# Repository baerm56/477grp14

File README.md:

# 477grp14
This is our senior design project

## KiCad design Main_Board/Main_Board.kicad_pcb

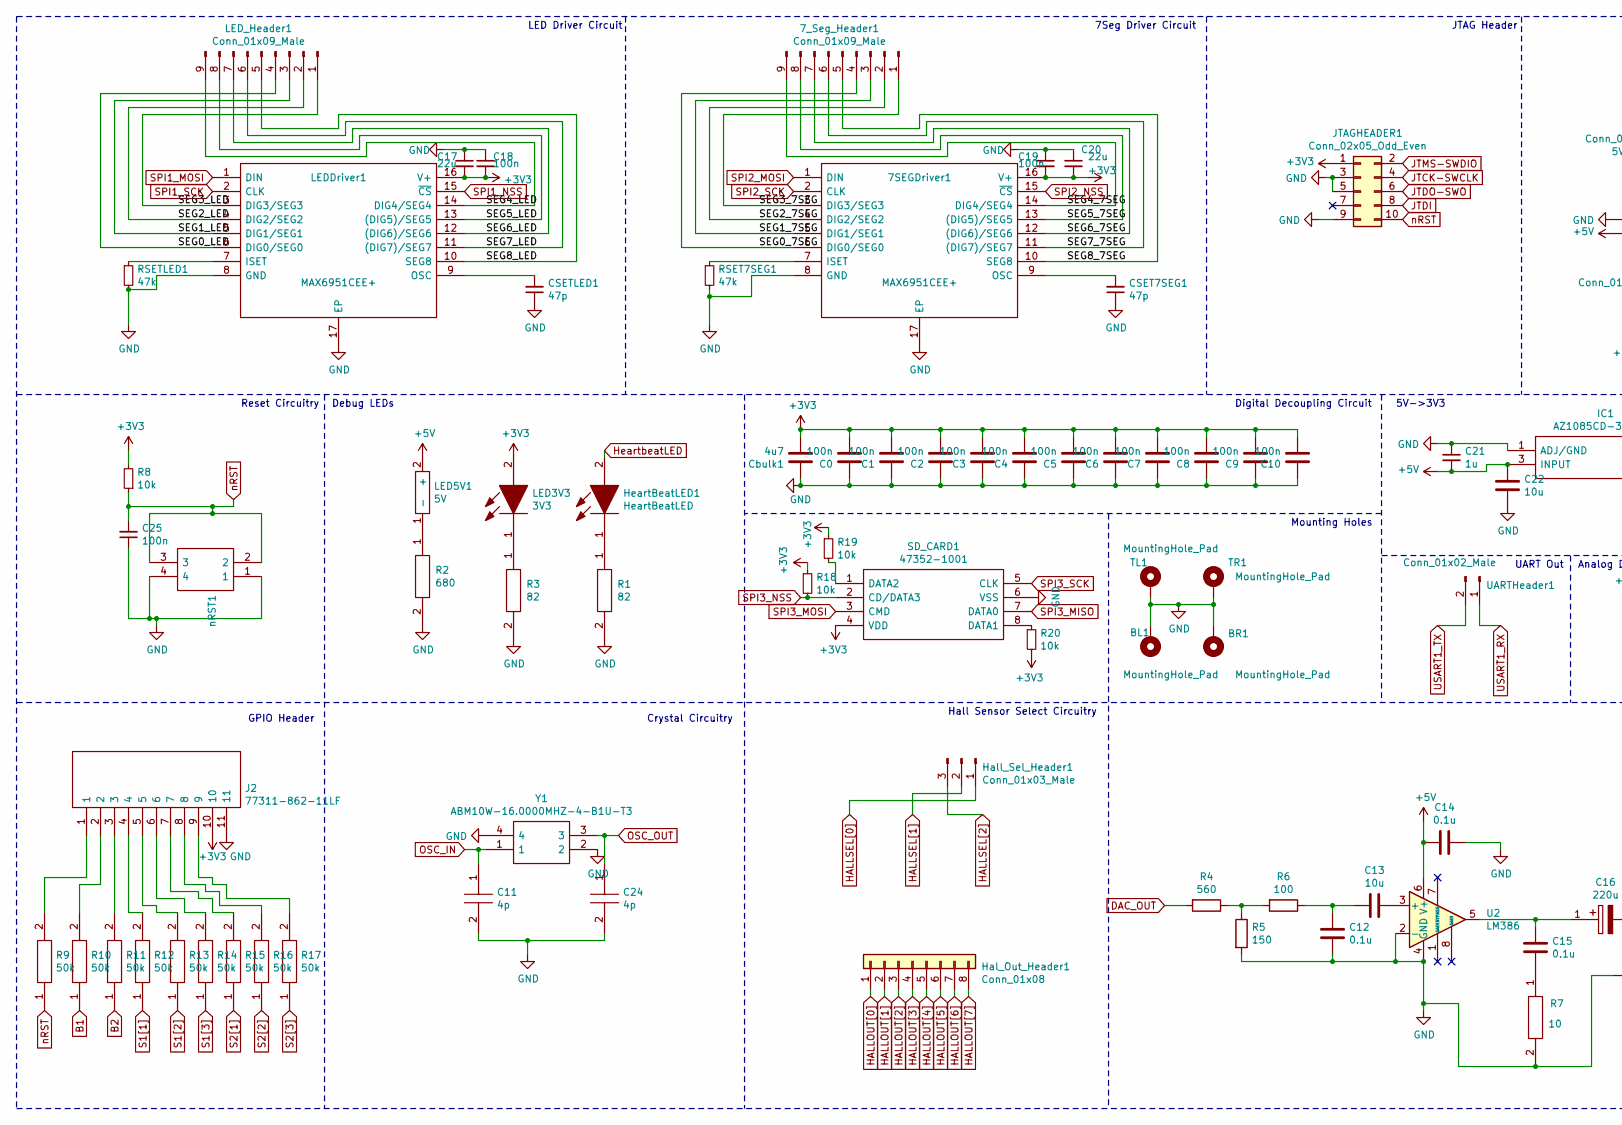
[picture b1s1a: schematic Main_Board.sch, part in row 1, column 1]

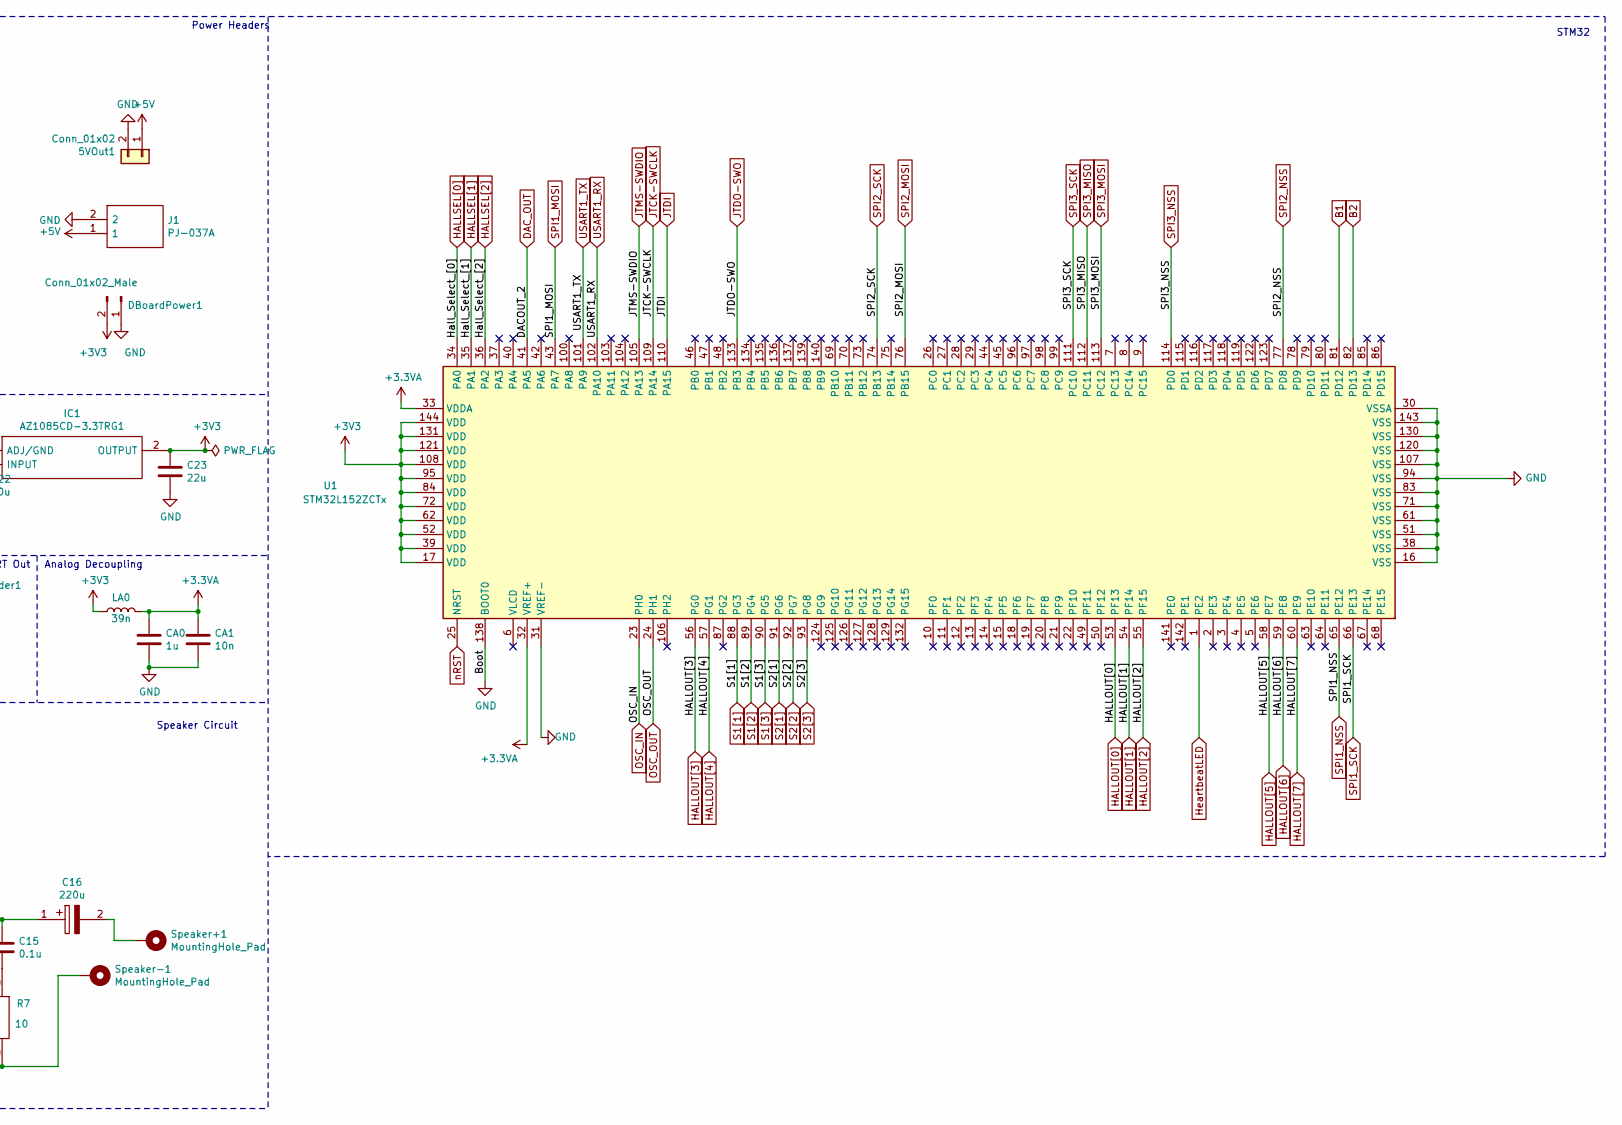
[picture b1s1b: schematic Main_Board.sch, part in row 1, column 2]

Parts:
5VOut1: Conn_01x02; PinHeader_1x02_P2.54mm_Vertical
7SEGDriver1: MAX6951CEE+; SOP64P602X173-17N; Mouser Part Number 700-MAX6951CEE
7_Seg_Header1: Conn_01x09_Male; PinHeader_1x09_P2.54mm_Vertical
BL1: MountingHole_Pad; MountingHole_4.3mm_M4_Pad_Via
BR1: MountingHole_Pad; MountingHole_4.3mm_M4_Pad_Via
C0, C1, C2, C3, C4, C5, C6, C7, C8, C9, C10, C18, C19, C25: 100n; CAPC2012X95N
C11, C24: 4p; CAPC1005X55N; Manufacturer_Part_Number GCQ1555C1H4R0CB01D
C12, C14, C15: 0.1u; CAPC2012X95N
C13, C22: 10u; CAPC2012X140N
C16: 220u; CAPPRD200W55D500H1200; Mouser Part Number 667-ECA-0JHG221B
C17, C20, C23: 22u; C1608_Commercial
C21: 1u; CAPC1005X55N
CA0: 1u; CAPC1005X55N
CA1: 10n; CAPC0402X22N
CSET7SEG1: 47p; CAPC2012X75N
CSETLED1: 47p; CAPC2012X75N
Cbulk1: 4u7; CAPPRD200W52D500H1250
DBoardPower1: Conn_01x02_Male; PinHeader_1x02_P2.54mm_Vertical
Hal_Out_Header1: Conn_01x08; PinHeader_1x08_P2.54mm_Vertical
Hall_Sel_Header1: Conn_01x03_Male; PinHeader_1x03_P2.54mm_Vertical
HeartBeatLED1: HeartBeatLED; LEDM168X65N; Mouser Part Number 755-SMLD12BN1WT86
IC1: AZ1085CD-3.3TRG1; AZ1085CD33TRG1; Mouser Part Number 621-AZ1085CD-3.3TRG1
J1: PJ-037A; PJ037A; Mouser Part Number 490-PJ-037A
J2: 77311-862-11LF; HDRV11W62P0X254_1X11_2794X240X853P; Manufacturer_Part_Number 77311-862-11LF
JTAGHEADER1: Conn_02x05_Odd_Even; PinHeader_2x05_P2.54mm_Vertical
LA0: 39n; LQW2UAS12NG00L
LED3V3: 3V3; LEDM168X65N; Mouser Part Number 755-SMLD12BN1WT86
LED5V1: 5V; HSMA-C380
LEDDriver1: MAX6951CEE+; SOP64P602X173-17N; Mouser Part Number 700-MAX6951CEE
LED_Header1: Conn_01x09_Male; PinHeader_1x09_P2.54mm_Vertical
R1, R3: 82; RESC6432X65N; Mouser Part Number 279-CRGP2512F82R
R2: 680; RESC3116X70N; Mouser Part Number 667-ERJ-UP8F6800V
R4: 560; CRGCQ2512F3K3
R5: 150; ERJ1TRQF1R0U
R6: 100; RESC5025X70N
R7: 10; RESC5025X120N; Mouser Part Number 279-350210RFT
R8, R18, R19, R20: 10k; RESC3116X70N
R9, R10, R11, R12, R13, R14, R15, R16, R17: 50k; RESC1005X40N; Mouser Part Number 71-CRCW0402-50K-E3
RSET7SEG1: 47k; RESC2012X60N
RSETLED1: 47k; RESC2012X60N
SD_CARD1: 47352-1001; Mouser Part Number 538-47352-1001
Speaker+1: MountingHole_Pad; MountingHole_2.5mm_Pad
Speaker-1: MountingHole_Pad; MountingHole_2.5mm_Pad
TL1: MountingHole_Pad; MountingHole_4.3mm_M4_Pad_Via
TR1: MountingHole_Pad; MountingHole_4.3mm_M4_Pad_Via
U1: STM32L152ZCTx; LQFP-144_20x20mm_P0.5mm
U2: LM386; SOIC127P600X175-8N
UARTHeader1: Conn_01x02_Male; PinHeader_1x02_P2.54mm_Vertical
Y1: ABM10W-16.0000MHZ-4-B1U-T3; ABM10W400000MHZ4K1ZT3; Mouser Part Number 815-10W16-4B1UT
nRST1: A; PTS647SM50SMTR2LFS; Mouser Part Number 611-PTS647SM50SMTR2L

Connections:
+3.3VA: CA0.1, CA1.1, LA0.2, U1.32 (VREF+), U1.33 (VDDA)
+3V3: 7SEGDriver1.16 (V+), C0.2, C1.2, C2.2, C3.2, C4.2, C5.2, C6.2, C7.2, C8.2, C9.2, C10.2, C17.2, C18.2, C19.2, C20.2, C23.1, Cbulk1.2, DBoardPower1.2, IC1.2 (OUTPUT), J2.10, JTAGHEADER1.1, LA0.1, LED3V3.2, LEDDriver1.16 (V+), R8.2, R18.1, R19.1, R20.2, SD_CARD1.4 (VDD), U1.17 (VDD), U1.39 (VDD), U1.52 (VDD), U1.62 (VDD), U1.72 (VDD), U1.84 (VDD), U1.95 (VDD), U1.108 (VDD), U1.121 (VDD), U1.131 (VDD), U1.144 (VDD)
+5V: 5VOut1.1, C14.2, C21.2, C22.1, IC1.3 (INPUT), J1.1, LED5V1.2 (+), U2.6 (V+)
/SEG0_7SEG: 7SEGDriver1.6 (DIG0/SEG0), 7_Seg_Header1.4
/SEG0_LED: LEDDriver1.6 (DIG0/SEG0), LED_Header1.4
/SEG1_7SEG: 7SEGDriver1.5 (DIG1/SEG1), 7_Seg_Header1.3
/SEG1_LED: LEDDriver1.5 (DIG1/SEG1), LED_Header1.3
/SEG2_7SEG: 7SEGDriver1.4 (DIG2/SEG2), 7_Seg_Header1.2
/SEG2_LED: LEDDriver1.4 (DIG2/SEG2), LED_Header1.2
/SEG3_7SEG: 7SEGDriver1.3 (DIG3/SEG3), 7_Seg_Header1.1
/SEG3_LED: LEDDriver1.3 (DIG3/SEG3), LED_Header1.1
/SEG4_7SEG: 7SEGDriver1.14 (DIG4/SEG4), 7_Seg_Header1.9
/SEG4_LED: LEDDriver1.14 (DIG4/SEG4), LED_Header1.9
/SEG5_7SEG: 7SEGDriver1.13 ((DIG5)/SEG5), 7_Seg_Header1.8
/SEG5_LED: LEDDriver1.13 ((DIG5)/SEG5), LED_Header1.8
/SEG6_7SEG: 7SEGDriver1.12 ((DIG6)/SEG6), 7_Seg_Header1.7
/SEG6_LED: LEDDriver1.12 ((DIG6)/SEG6), LED_Header1.7
/SEG7_7SEG: 7SEGDriver1.11 ((DIG7)/SEG7), 7_Seg_Header1.6
/SEG7_LED: LEDDriver1.11 ((DIG7)/SEG7), LED_Header1.6
/SEG8_7SEG: 7SEGDriver1.10 (SEG8), 7_Seg_Header1.5
/SEG8_LED: LEDDriver1.10 (SEG8), LED_Header1.5
B1: R10.1, U1.81 (PD12)
B2: R11.1, U1.82 (PD13)
DAC_OUT: R4.2, U1.41 (PA5)
GND: 5VOut1.2, 7SEGDriver1.8 (GND), 7SEGDriver1.17 (EP), BL1.1, BR1.1, C0.1, C1.1, C2.1, C3.1, C4.1, C5.1, C6.1, C7.1, C8.1, C9.1, C10.1, C11.2, C12.2, C14.1, C17.1, C18.1, C19.1, C20.1, C21.1, C22.2, C23.2, C24.2, C25.1, CA0.2, CA1.2, CSET7SEG1.1, CSETLED1.1, Cbulk1.1, DBoardPower1.1, IC1.1 (ADJ/GND), J1.2, J2.11, JTAGHEADER1.3, JTAGHEADER1.5, JTAGHEADER1.9, LEDDriver1.8 (GND), LEDDriver1.17 (EP), R1.2, R2.2, R3.2, R5.2, R7.2, RSET7SEG1.2, RSETLED1.2, SD_CARD1.6 (VSS), Speaker-1.1, TL1.1, TR1.1, U1.16 (VSS), U1.30 (VSSA), U1.31 (VREF-), U1.38 (VSS), U1.51 (VSS), U1.61 (VSS), U1.71 (VSS), U1.83 (VSS), U1.94 (VSS), U1.107 (VSS), U1.120 (VSS), U1.130 (VSS), U1.138 (BOOT0), U1.143 (VSS), U2.2 (-), U2.4 (GND), Y1.2, Y1.4, nRST1.1, nRST1.4
HALLOUT[0]: Hal_Out_Header1.1, U1.53 (PF13)
HALLOUT[1]: Hal_Out_Header1.2, U1.54 (PF14)
HALLOUT[2]: Hal_Out_Header1.3, U1.55 (PF15)
HALLOUT[3]: Hal_Out_Header1.4, U1.56 (PG0)
HALLOUT[4]: Hal_Out_Header1.5, U1.57 (PG1)
HALLOUT[5]: Hal_Out_Header1.6, U1.58 (PE7)
HALLOUT[6]: Hal_Out_Header1.7, U1.59 (PE8)
HALLOUT[7]: Hal_Out_Header1.8, U1.60 (PE9)
HALLSEL[0]: Hall_Sel_Header1.1, U1.34 (PA0)
HALLSEL[1]: Hall_Sel_Header1.2, U1.35 (PA1)
HALLSEL[2]: Hall_Sel_Header1.3, U1.36 (PA2)
HeartbeatLED: HeartBeatLED1.2, U1.1 (PE2)
JTCK-SWCLK: JTAGHEADER1.4, U1.109 (PA14)
JTDI: JTAGHEADER1.8, U1.110 (PA15)
JTDO-SWO: JTAGHEADER1.6, U1.133 (PB3)
JTMS-SWDIO: JTAGHEADER1.2, U1.105 (PA13)
unnamed: 7SEGDriver1.7 (ISET), RSET7SEG1.1
unnamed: 7SEGDriver1.9 (OSC), CSET7SEG1.2
unnamed: C12.1, C13.2, R6.1
unnamed: C13.1, U2.3 (+)
unnamed: C15.1, C16.1, U2.5
unnamed: C15.2, R7.1
unnamed: C16.2, Speaker+1.1
unnamed: CSETLED1.2, LEDDriver1.9 (OSC)
unnamed: HeartBeatLED1.1, R1.1
unnamed: J2.1, R9.2
unnamed: J2.2, R10.2
unnamed: J2.3, R11.2
unnamed: J2.4, R12.2
unnamed: J2.5, R13.2
unnamed: J2.6, R14.2
unnamed: J2.7, R15.2
unnamed: J2.8, R16.2
unnamed: J2.9, R17.2
unnamed: LED3V3.1, R3.1
unnamed: LED5V1.1 (-), R2.1
unnamed: LEDDriver1.7 (ISET), RSETLED1.1
unnamed: R4.1, R5.1, R6.2
unnamed: R19.2, SD_CARD1.1 (DATA2)
unnamed: R20.1, SD_CARD1.8 (DATA1)
OSC_IN: C11.1, U1.23 (PH0), Y1.1
OSC_OUT: C24.1, U1.24 (PH1), Y1.3
S1[1]: R12.1, U1.88 (PG3)
S1[2]: R13.1, U1.89 (PG4)
S1[3]: R14.1, U1.90 (PG5)
S2[1]: R15.1, U1.91 (PG6)
S2[2]: R16.1, U1.92 (PG7)
S2[3]: R17.1, U1.93 (PG8)
SPI1_MOSI: LEDDriver1.1 (DIN), U1.43 (PA7)
SPI1_NSS: LEDDriver1.15 (~CS), U1.65 (PE12)
SPI1_SCK: LEDDriver1.2 (CLK), U1.66 (PE13)
SPI2_MOSI: 7SEGDriver1.1 (DIN), U1.76 (PB15)
SPI2_NSS: 7SEGDriver1.15 (~CS), U1.77 (PD8)
SPI2_SCK: 7SEGDriver1.2 (CLK), U1.74 (PB13)
SPI3_MISO: SD_CARD1.7 (DATA0), U1.112 (PC11)
SPI3_MOSI: SD_CARD1.3 (CMD), U1.113 (PC12)
SPI3_NSS: R18.2, SD_CARD1.2 (CD/DATA3), U1.114 (PD0)
SPI3_SCK: SD_CARD1.5 (CLK), U1.111 (PC10)
USART1_RX: U1.102 (PA10), UARTHeader1.1
USART1_TX: U1.101 (PA9), UARTHeader1.2
nRST: C25.2, JTAGHEADER1.10, R8.1, R9.1, U1.25 (NRST), nRST1.2, nRST1.3

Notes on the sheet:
Digital Decoupling Circuit
5V->3V3
Analog Decoupling
LED Driver Circuit
7Seg Driver Circuit
JTAG Header
STM32
UART Out
Hall Sensor Select Circuitry
Reset Circuitry
GPIO Header
Debug LEDs
Crystal Circuitry
Power Headers
Mounting Holes
Speaker Circuit

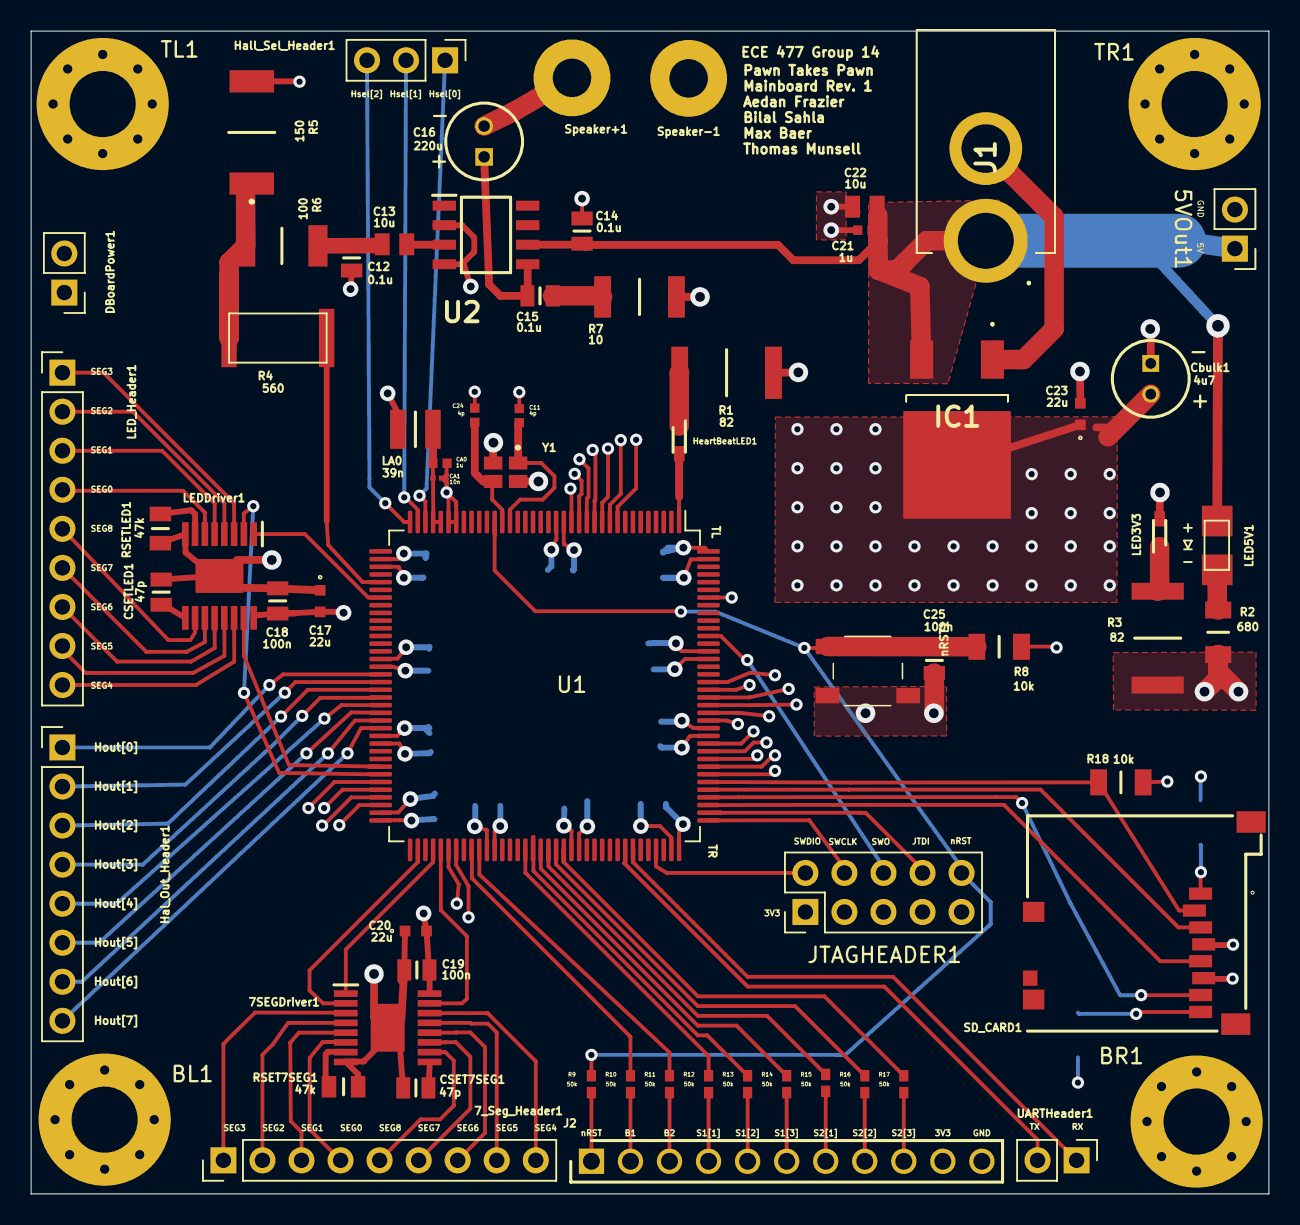
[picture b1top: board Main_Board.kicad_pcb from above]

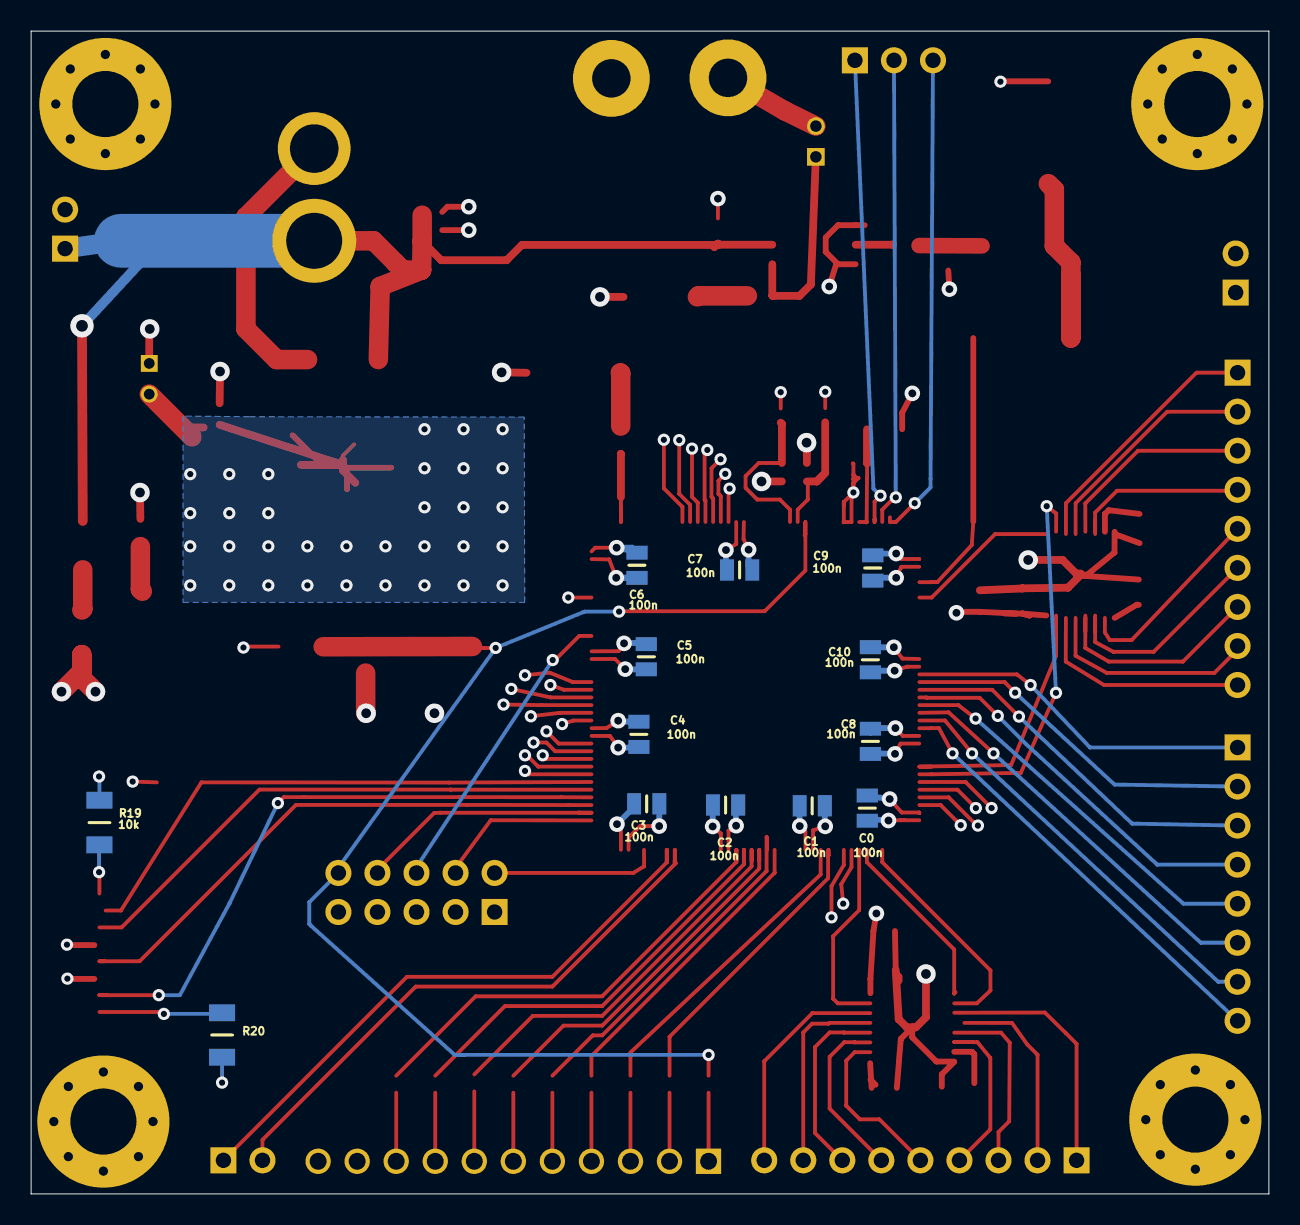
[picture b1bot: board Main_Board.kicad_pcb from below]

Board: 4 copper layers, 80.5 x 75.6 mm, 81 parts (13 on the bottom side), 86 nets.

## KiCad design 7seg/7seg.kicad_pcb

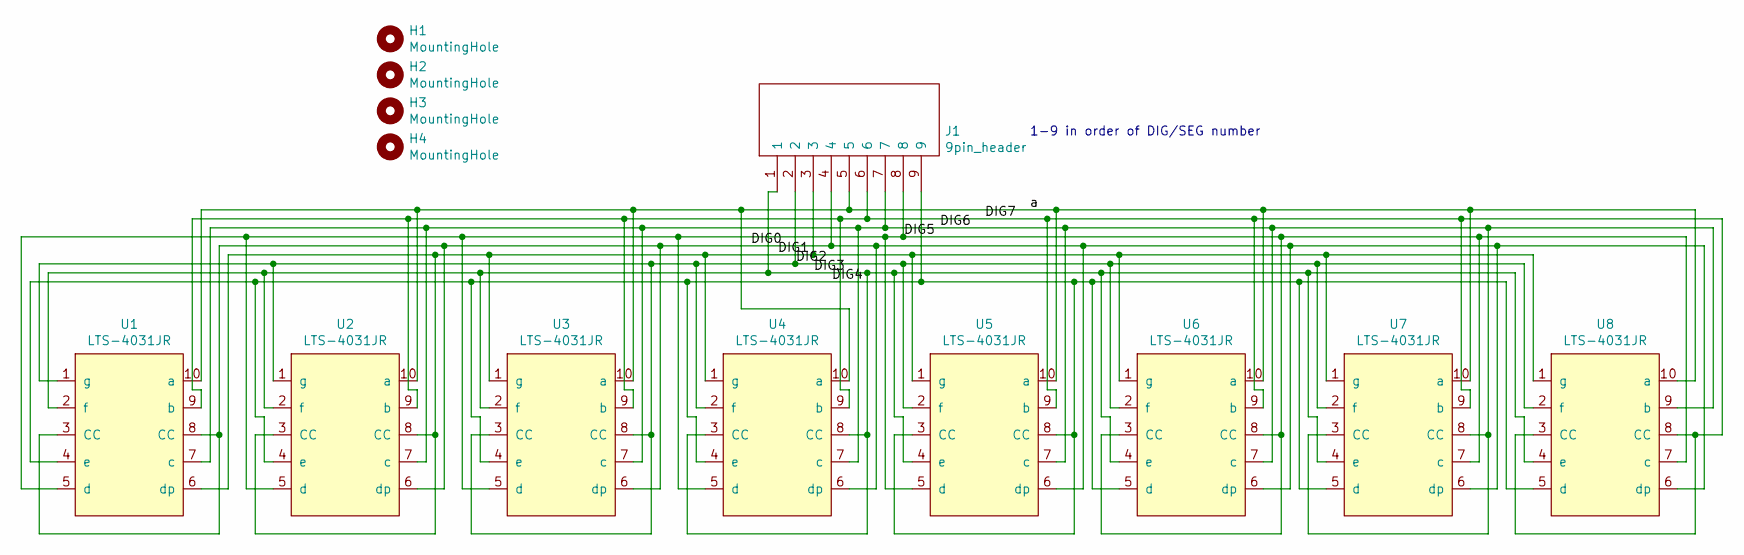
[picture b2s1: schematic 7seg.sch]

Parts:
H1, H2, H3, H4: MountingHole; MountingHole_2.2mm_M2_Pad
J1: 9pin_header; header; Manufacturer_Part_Number 825433-9; Mouser Part Number 571-825433-9
U1, U2, U3, U4, U5, U6, U7, U8: LTS-4031JR; 7seg

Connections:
/DIG0: J1.4, U1.3 (CC), U1.8 (CC), U2.6 (dp), U3.6 (dp), U4.6 (dp), U5.6 (dp), U6.6 (dp), U7.6 (dp), U8.6 (dp)
/DIG1: J1.3, U1.6 (dp), U2.3 (CC), U2.8 (CC), U3.1 (g), U4.1 (g), U5.1 (g), U6.1 (g), U7.1 (g), U8.1 (g)
/DIG2: J1.2, U1.1 (g), U2.1 (g), U3.3 (CC), U3.8 (CC), U4.2 (f), U5.2 (f), U6.2 (f), U7.2 (f), U8.2 (f)
/DIG3: J1.1, U1.2 (f), U2.2 (f), U3.2 (f), U4.3 (CC), U4.8 (CC), U5.4 (e), U6.4 (e), U7.4 (e), U8.4 (e)
/DIG4: J1.9, U1.4 (e), U2.4 (e), U3.4 (e), U4.4 (e), U5.3 (CC), U5.8 (CC), U6.5 (d), U7.5 (d), U8.5 (d)
/DIG5: J1.8, U1.5 (d), U2.5 (d), U3.5 (d), U4.5 (d), U5.5 (d), U6.3 (CC), U6.8 (CC), U7.7 (c), U8.7 (c)
/DIG6: J1.7, U1.7 (c), U2.7 (c), U3.7 (c), U4.7 (c), U5.7 (c), U6.7 (c), U7.3 (CC), U7.8 (CC), U8.9 (b)
/DIG7: J1.6, U1.9 (b), U2.9 (b), U3.9 (b), U4.9 (b), U5.9 (b), U6.9 (b), U7.9 (b), U8.3 (CC), U8.8 (CC)
/a: J1.5, U1.10 (a), U2.10 (a), U3.10 (a), U4.10 (a), U5.10 (a), U6.10 (a), U7.10 (a), U8.10 (a)

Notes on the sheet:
1-9 in order of DIG/SEG number

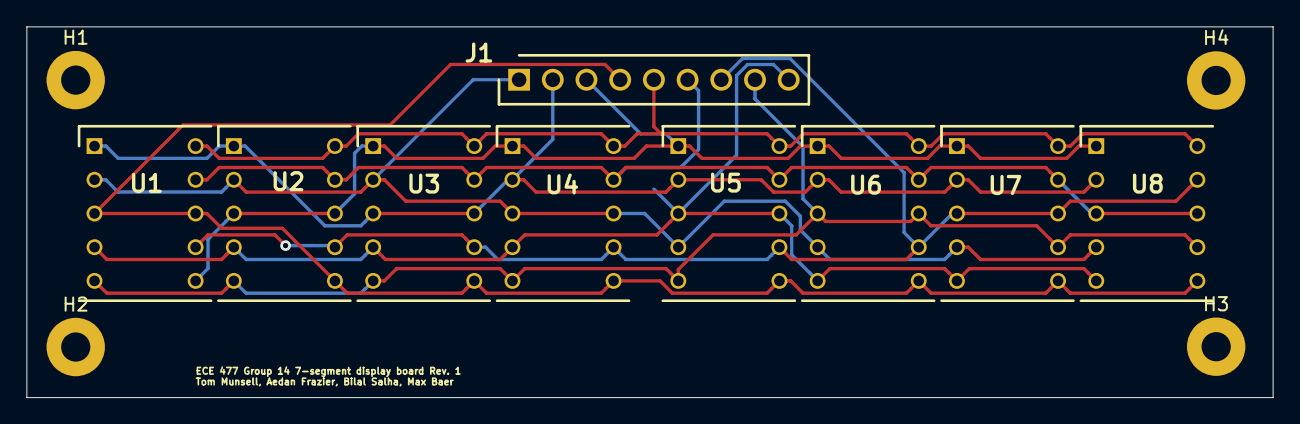
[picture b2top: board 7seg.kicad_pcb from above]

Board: 2 copper layers, 93.9 x 27.9 mm, 13 parts (0 on the bottom side), 9 nets.

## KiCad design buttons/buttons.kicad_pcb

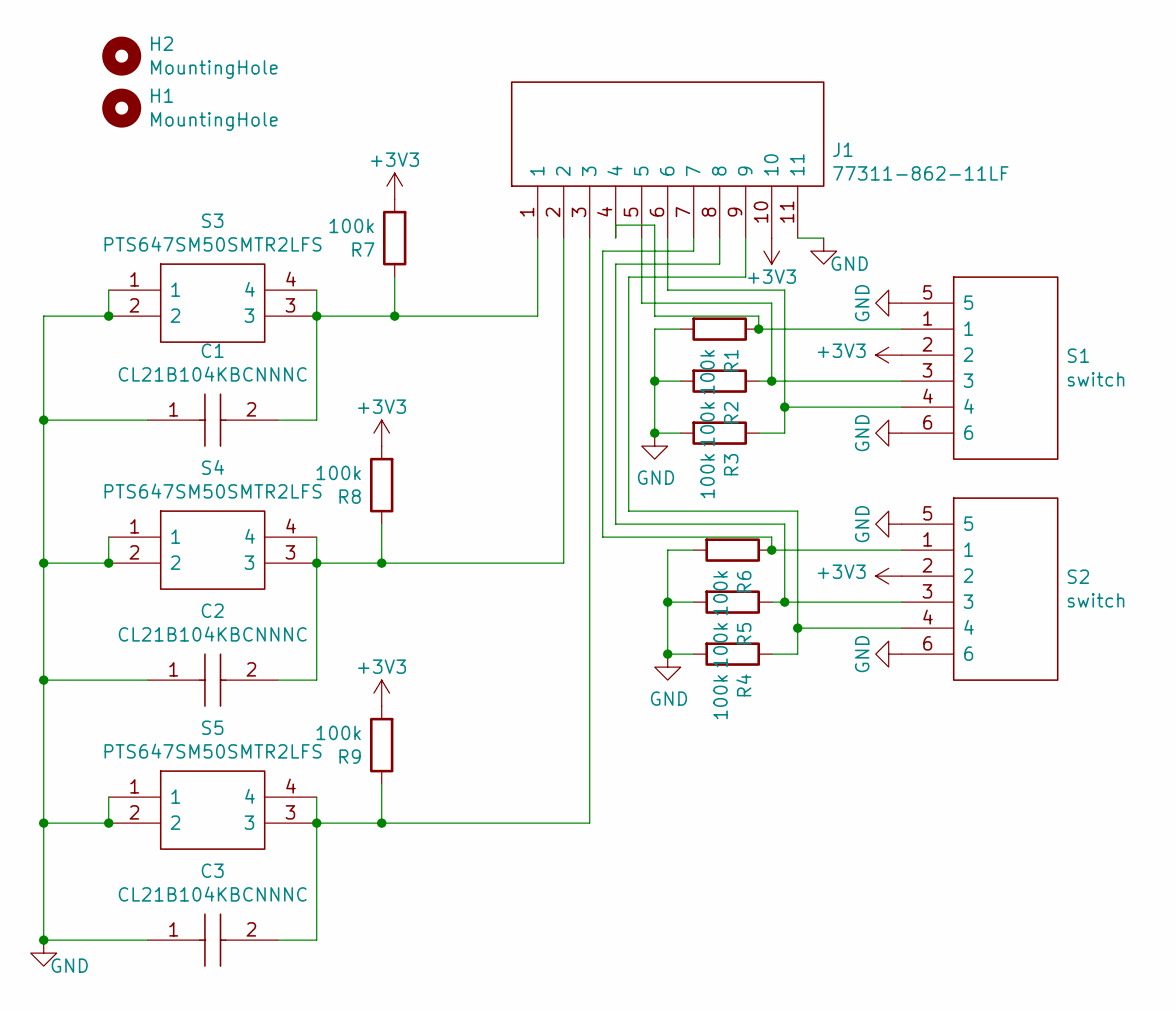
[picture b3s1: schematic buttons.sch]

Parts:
C1, C2, C3: CL21B104KBCNNNC; CAPC2012X95N; Mouser Part Number 187-CL21B104KBCNNNC
H1, H2: MountingHole; MountingHole_3.2mm_M3_Pad
J1: 77311-862-11LF; HDRV11W62P0X254_1X11_2794X240X853P; Manufacturer_Part_Number 77311-862-11LF
R1, R2, R3, R4, R5, R6, R7, R8, R9: 100k; RESC3116X70N
S1, S2: switch; Mouser Part Number 611-OS103011MS8QP1
S3, S4, S5: PTS647SM50SMTR2LFS; Mouser Part Number 611-PTS647SM50SMTR2L

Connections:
+3V3: J1.10, R7.2, R8.2, R9.2, S1.2, S2.2
GND: C1.1, C2.1, C3.1, J1.11, R1.2, R2.2, R3.2, R4.2, R5.2, R6.2, S1.5, S1.6, S2.5, S2.6, S3.1, S3.2, S4.1, S4.2, S5.1, S5.2
unnamed: C1.2, J1.1, R7.1, S3.3, S3.4
unnamed: C2.2, J1.2, R8.1, S4.3, S4.4
unnamed: C3.2, J1.3, R9.1, S5.3, S5.4
unnamed: J1.4, R1.1, S1.1
unnamed: J1.5, R2.1, S1.3
unnamed: J1.6, R3.1, S1.4
unnamed: J1.7, R6.1, S2.1
unnamed: J1.8, R5.1, S2.3
unnamed: J1.9, R4.1, S2.4

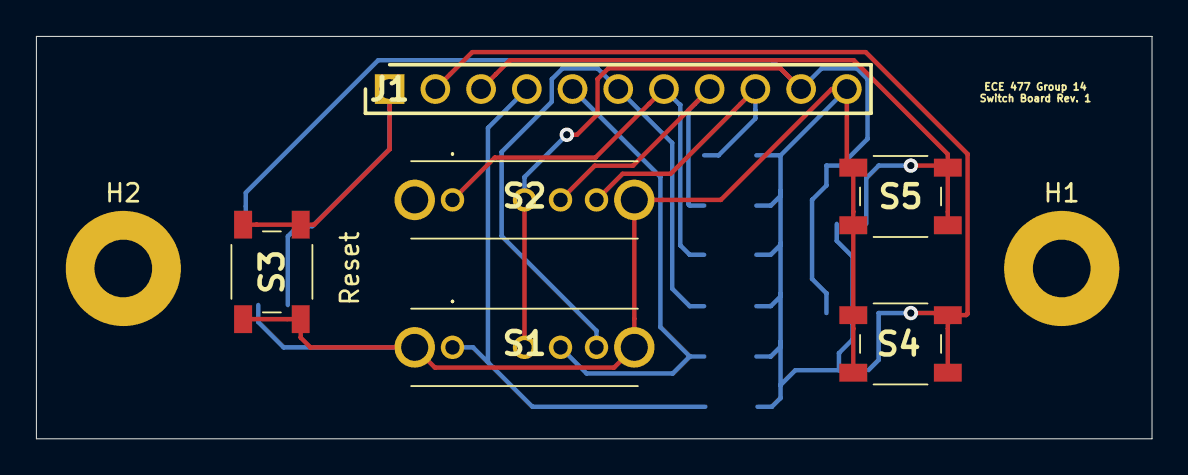
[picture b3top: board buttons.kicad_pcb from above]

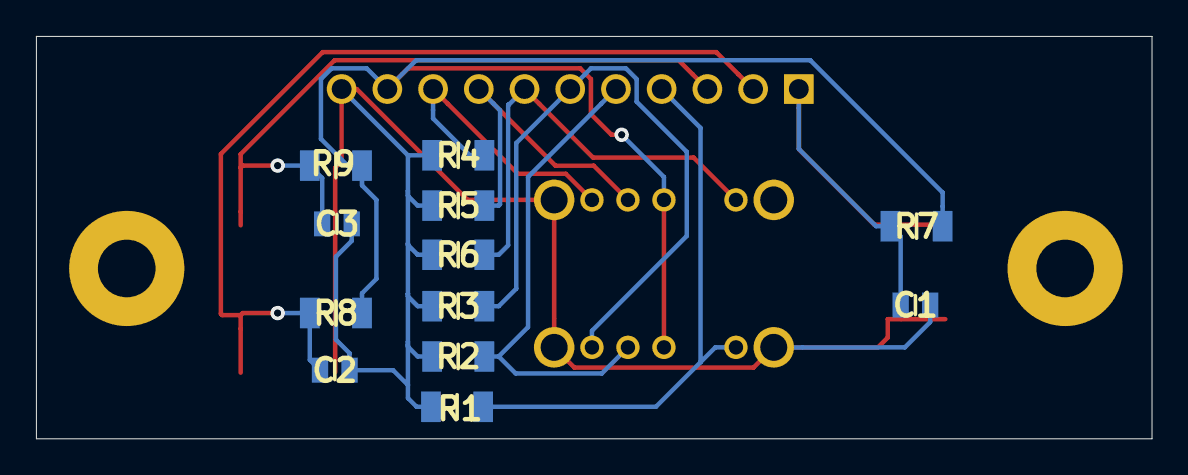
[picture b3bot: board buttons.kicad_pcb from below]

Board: 2 copper layers, 62.0 x 22.4 mm, 20 parts (12 on the bottom side), 11 nets.

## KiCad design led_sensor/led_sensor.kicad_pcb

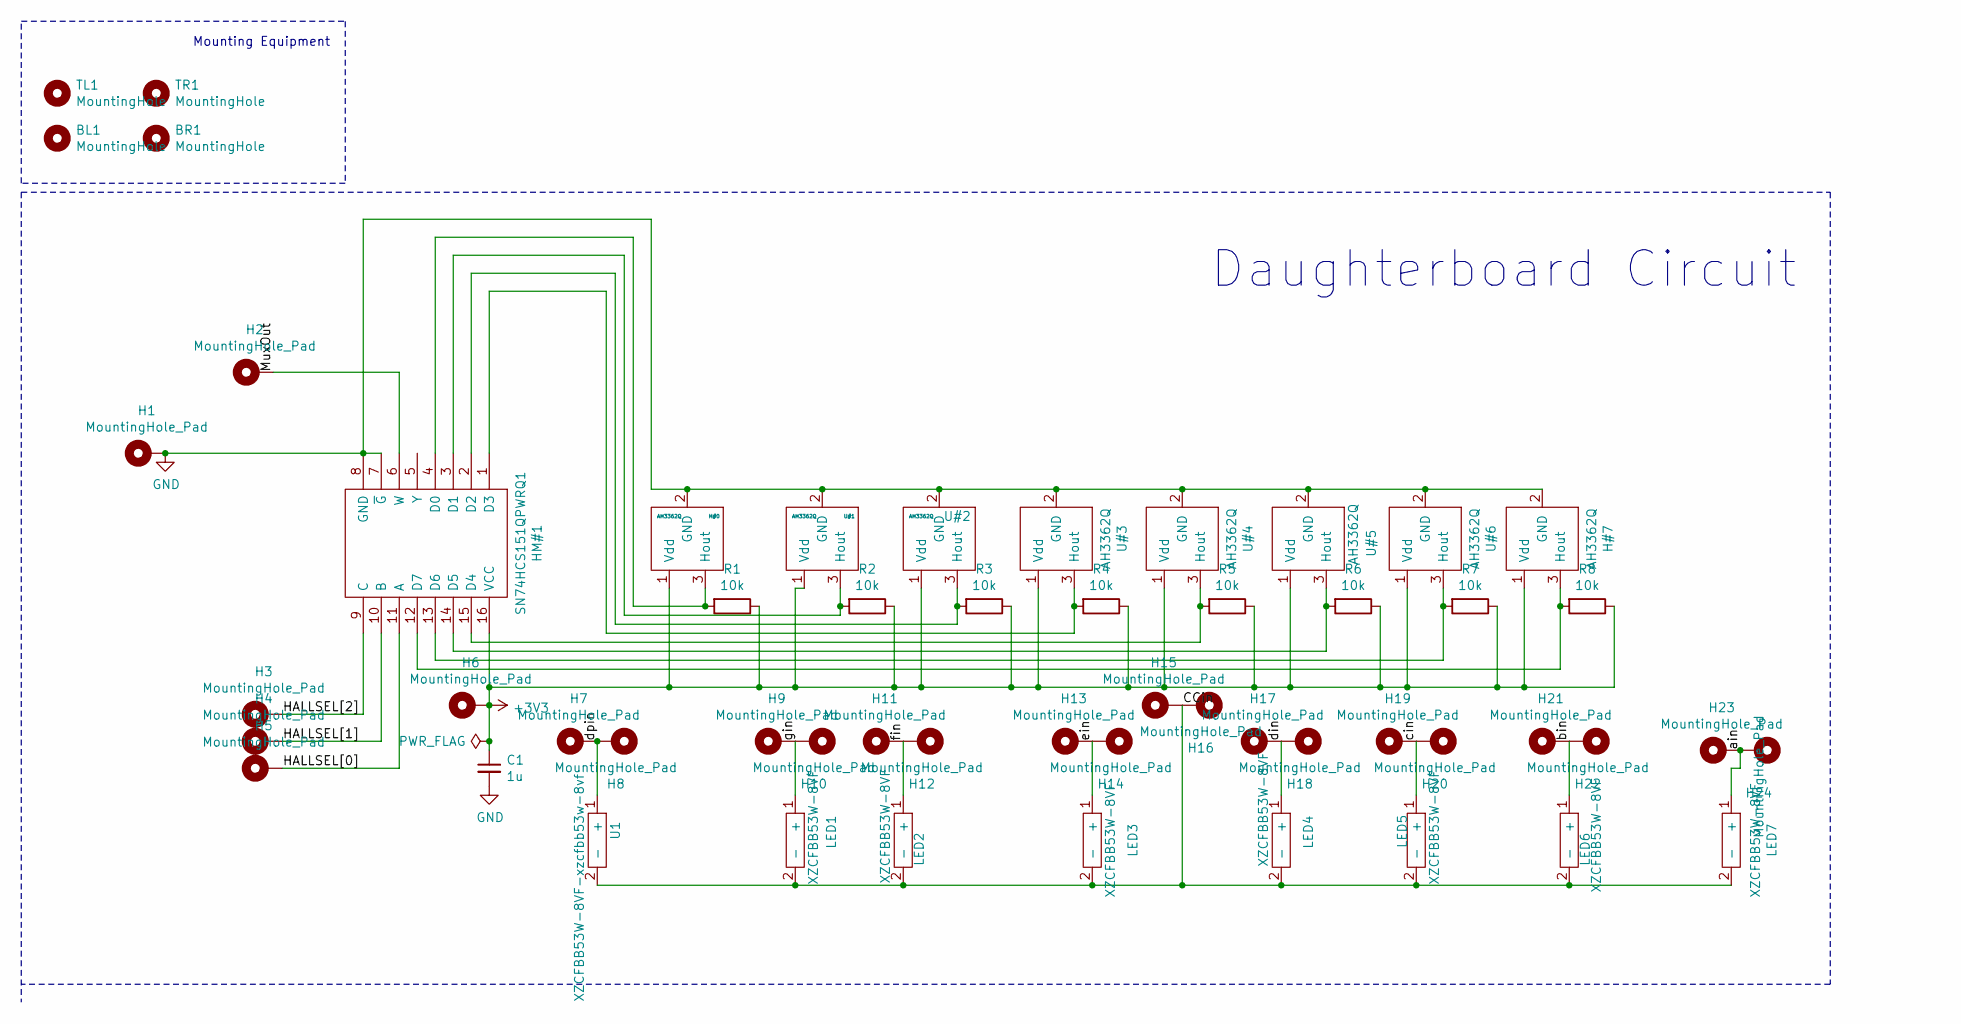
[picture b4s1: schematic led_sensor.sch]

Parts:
BL1: MountingHole; MountingHole_2.2mm_M2
BR1: MountingHole; MountingHole_2.2mm_M2
C1: 1u; CAPC1005X55N
H1, H2, H3, H4, H5, H6, H7, H8, H9, H10, H11, H12, H13, H14, H15, H16, H17, H18, H19, H20, H21, H22, H23, H24: MountingHole_Pad; SolderWirePad_1x01_SMD_5x10mm
H#0, H#7: AH3362Q; AH3662Q
HM#1: SN74HCS151QPWRQ1; SOP65P640X120-16N; Manufacturer_Part_Number SN74HCS151QPWRQ1; Mouser Part Number 595-SN74HCS151QPWRQ1
LED1, LED2, LED3, LED4, LED5, LED6, LED7: XZCFBB53W-8VF; HSMA-C380
R1, R2, R3, R4, R5, R6, R7, R8: 10k; RESC1608X55N
TL1: MountingHole; MountingHole_2.2mm_M2
TR1: MountingHole; MountingHole_2.2mm_M2
U1: XZCFBB53W-8VF-xzcfbb53w-8vf; HSMA-C380
U#1, U#2, U#3, U#4, U#5, U#6: AH3362Q; AH3662Q

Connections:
+3V3: C1.1, H6.1, H#0.1 (Vdd), H#7.1 (Vdd), HM#1.16 (VCC), R1.1, R2.1, R3.1, R4.1, R5.1, R6.1, R7.1, R8.1, U#1.1 (Vdd), U#2.1 (Vdd), U#3.1 (Vdd), U#4.1 (Vdd), U#5.1 (Vdd), U#6.1 (Vdd)
/CCin: H15.1, H16.1, LED1.2 (-), LED2.2 (-), LED3.2 (-), LED4.2 (-), LED5.2 (-), LED6.2 (-), LED7.2 (-), U1.2 (-); also elsewhere on the board
/HALLSEL[0]: H5.1, HM#1.11 (A)
/HALLSEL[1]: H4.1, HM#1.10 (B)
/HALLSEL[2]: H3.1, HM#1.9 (C)
/MuxOut: H2.1, HM#1.6 (W)
/ain: H23.1, H24.1, LED7.1 (+)
/bin: H21.1, H22.1, LED6.1 (+)
/cin: H19.1, H20.1, LED5.1 (+)
/din: H17.1, H18.1, LED4.1 (+)
/dpin: H7.1, H8.1, U1.1 (+); also elsewhere on the board
/ein: H13.1, H14.1, LED3.1 (+)
/fin: H11.1, H12.1, LED2.1 (+)
/gin: H9.1, H10.1, LED1.1 (+)
GND: C1.2, H1.1, H#0.2 (GND), H#7.2 (GND), HM#1.7 (~G), HM#1.8 (GND), U#1.2 (GND), U#2.2 (GND), U#3.2 (GND), U#4.2 (GND), U#5.2 (GND), U#6.2 (GND)
unnamed: H#0.3 (Hout), HM#1.4 (D0), R1.2
unnamed: H#7.3 (Hout), HM#1.12 (D7), R8.2
unnamed: HM#1.1 (D3), R4.2, U#3.3 (Hout)
unnamed: HM#1.2 (D2), R3.2, U#2.3 (Hout)
unnamed: HM#1.3 (D1), R2.2, U#1.3 (Hout)
unnamed: HM#1.13 (D6), R7.2, U#6.3 (Hout)
unnamed: HM#1.14 (D5), R6.2, U#5.3 (Hout)
unnamed: HM#1.15 (D4), R5.2, U#4.3 (Hout)

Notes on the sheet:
Mounting Equipment
Daughterboard Circuit

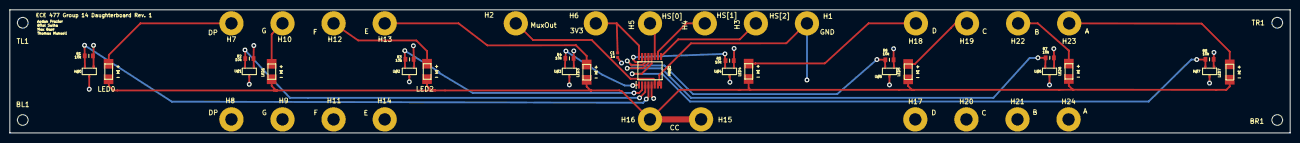
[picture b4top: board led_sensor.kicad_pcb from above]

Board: 4 copper layers, 264.2 x 25.4 mm, 54 parts (0 on the bottom side), 23 nets.

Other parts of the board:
LED0: XZCFBB53W-8VF-xzcfbb53w-8vf; HSMA-C380

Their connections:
/CCin: LED0.2; also elsewhere on the board
/dpin: LED0.1; also elsewhere on the board

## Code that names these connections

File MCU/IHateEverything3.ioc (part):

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Mcu.Name=STM32L152ZCTx
Mcu.Package=LQFP144
Mcu.UserName=STM32L152ZCTx
PA0-WKUP1.GPIOParameters=GPIO_Label
PA0-WKUP1.GPIO_Label=HALLSEL0
PA0-WKUP1.Signal=GPIO_Output
PA1.GPIOParameters=GPIO_Label
PA1.GPIO_Label=HALLSEL1
PA1.Signal=GPIO_Output
PA10.Mode=Asynchronous
PA10.Signal=USART1_RX
PA13.Mode=Serial_Wire
PA13.Signal=SYS_JTMS-SWDIO
PA14.Mode=Serial_Wire
PA14.Signal=SYS_JTCK-SWCLK
PA2.GPIOParameters=GPIO_Label
PA2.GPIO_Label=HALLSEL2
PA2.Signal=GPIO_Output
PA5.Signal=COMP_DAC2_group
PA6.Mode=Full_Duplex_Master
PA6.Signal=SPI1_MISO
PA7.Mode=Full_Duplex_Master
PA7.Signal=SPI1_MOSI
PA9.Mode=Asynchronous
PA9.Signal=USART1_TX
PB13.Mode=Full_Duplex_Master
PB13.Signal=SPI2_SCK
PB14.Mode=Full_Duplex_Master
PB14.Signal=SPI2_MISO
PB15.Mode=Full_Duplex_Master
PB15.Signal=SPI2_MOSI
PC10.Mode=Full_Duplex_Master
PC10.Signal=SPI3_SCK
PC11.Mode=Full_Duplex_Master
PC11.Signal=SPI3_MISO
PC12.Mode=Full_Duplex_Master
PC12.Signal=SPI3_MOSI
PD0.GPIOParameters=GPIO_Label
PD0.GPIO_Label=SD_CS
PD0.Signal=GPIO_Output
PD12.GPIOParameters=GPIO_Label,GPIO_ModeDefaultEXTI
PD12.GPIO_Label=BUTTON1
PD12.GPIO_ModeDefaultEXTI=GPIO_MODE_IT_FALLING
PD12.Signal=GPXTI12
PD13.GPIOParameters=GPIO_Label,GPIO_ModeDefaultEXTI
PD13.GPIO_Label=BUTTON2
PD13.GPIO_ModeDefaultEXTI=GPIO_MODE_IT_FALLING
PD13.Signal=GPXTI13
PD8.Signal=GPIO_Output
PE12.Signal=GPIO_Output
PE13.Mode=Full_Duplex_Master
PE13.Signal=SPI1_SCK
PE2.GPIOParameters=PinState,GPIO_Label
PE2.GPIO_Label=HEARTBEAT_LED
PE2.PinState=GPIO_PIN_SET
PE2.Signal=GPIO_Output
PE7.GPIOParameters=GPIO_Label
PE7.GPIO_Label=HALLOUT5
PE7.Signal=GPIO_Input
PE8.GPIOParameters=GPIO_Label
PE8.GPIO_Label=HALLOUT6
PE8.Signal=GPIO_Input
PE9.GPIOParameters=GPIO_Label
PE9.GPIO_Label=HALLOUT7
PE9.Signal=GPIO_Input
PF13.GPIOParameters=GPIO_Label
PF13.GPIO_Label=HALLOUT0
PF13.Signal=GPIO_Input
PF14.GPIOParameters=GPIO_Label
PF14.GPIO_Label=HALLOUT1
PF14.Signal=GPIO_Input
PF15.GPIOParameters=GPIO_Label
PF15.GPIO_Label=HALLOUT2
PF15.Signal=GPIO_Input
PG0.GPIOParameters=GPIO_Label
PG0.GPIO_Label=HALLOUT3
PG0.Signal=GPIO_Input
PG1.GPIOParameters=GPIO_Label
PG1.GPIO_Label=HALLOUT4
PG1.Signal=GPIO_Input
PG3.GPIOParameters=GPIO_Label
PG3.GPIO_Label=SWITCH1_1
PG3.Signal=GPIO_Input
PG4.GPIOParameters=GPIO_Label
PG4.GPIO_Label=SWITCH1_2
PG4.Signal=GPIO_Input
PG5.GPIOParameters=GPIO_Label
PG5.GPIO_Label=SWITCH1_3
PG5.Signal=GPIO_Input
PG6.GPIOParameters=GPIO_Label,GPIO_ModeDefaultEXTI
PG6.GPIO_Label=SWITCH2_1
PG6.GPIO_ModeDefaultEXTI=GPIO_MODE_IT_FALLING
PG6.Signal=GPXTI6
PG7.GPIOParameters=GPIO_Label,GPIO_ModeDefaultEXTI
PG7.GPIO_Label=SWITCH2_2
PG7.GPIO_ModeDefaultEXTI=GPIO_MODE_IT_FALLING
PG7.Signal=GPXTI7
PG8.GPIOParameters=GPIO_Label,GPIO_ModeDefaultEXTI
PG8.GPIO_Label=SWITCH2_3
PG8.GPIO_ModeDefaultEXTI=GPIO_MODE_IT_FALLING
PG8.Signal=GPXTI8
RCC.HSE_VALUE=24000000
RCC.SYSCLKFreq_VALUE=32000000
RCC.SYSCLKSource=RCC_SYSCLKSOURCE_PLLCLK
board=custom

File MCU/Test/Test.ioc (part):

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Mcu.Name=STM32L152RETx
Mcu.Package=LQFP64
Mcu.UserName=STM32L152RETx
PA13.Mode=Serial_Wire
PA13.Signal=SYS_JTMS-SWDIO
PA14.Mode=Serial_Wire
PA14.Signal=SYS_JTCK-SWCLK
PA4.Signal=COMP_DAC1_group
PA5.Mode=Full_Duplex_Master
PA5.Signal=SPI1_SCK
PA6.Mode=Full_Duplex_Master
PA6.Signal=SPI1_MISO
PA7.Mode=Full_Duplex_Master
PA7.Signal=SPI1_MOSI
PB1.GPIOParameters=GPIO_Label
PB1.GPIO_Label=SD_CS
PB1.Signal=GPIO_Output
PB13.Mode=Full_Duplex_Master
PB13.Signal=SPI2_SCK
PB14.Mode=Full_Duplex_Master
PB14.Signal=SPI2_MISO
PB15.Mode=Full_Duplex_Master
PB15.Signal=SPI2_MOSI
PB6.GPIOParameters=PinState
PB6.PinState=GPIO_PIN_SET
PB6.Signal=GPIO_Output
PH0-OSC_IN.Mode=HSE-External-Oscillator
PH0-OSC_IN.Signal=RCC_OSC_IN
PH1-OSC_OUT.Mode=HSE-External-Oscillator
PH1-OSC_OUT.Signal=RCC_OSC_OUT
RCC.HSE_VALUE=24000000
RCC.SYSCLKFreq_VALUE=32000000
RCC.SYSCLKSource=RCC_SYSCLKSOURCE_PLLCLK
board=custom

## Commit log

2021-09-03 Added files
2021-09-03 Updated code to be modular for easier use in the future
2021-09-24 Added STM32 files
2021-09-27 removed unneeded files
2021-09-27 Added all MCU code
2021-09-27 Added new LED script
2021-09-29 Updated STM code
2021-09-29 Added SPI test
2021-09-30 Wrote some LED code
2021-09-30 Weird readme bug
2021-10-01 PCB Stuff
2021-10-03 Working on DMA
2021-10-03 Git hates me
2021-10-04 DAC and DMA now working
2021-10-05 Updated PCB
2021-10-05 Updated tracker code.
2021-10-06 SD card works and DAC sounds okay-ish
2021-10-07 added 7-segment schematic
2021-10-07 Updated Mainboard
2021-10-07 Got audio working with diferent frequencies and made code cleaner
2021-10-11 7-segment layout
2021-10-11 7-segment footprints
2021-10-11 add rescued symbols so kicad doesn't complain every time?
2021-10-11 add rescued symbols so kicad doesn't complain every time? 2
2021-10-11 Revert first symbol rescue change.
    This reverts commit da5e3b956d62bf000f607909d73018914190f8b5.
2021-10-12 Added switch board, reset circuit
2021-10-12 more library changes
2021-10-12 8 Hall Sensor
2021-10-13 ''Updates 12-10"
2021-10-13 Parts Libs
2021-10-13 fixed reverse biased LEDs
2021-10-13 added DC jack, miscellaneous
2021-10-13 cleaned up directories, silkscreen
2021-10-13 changed LM386 package to match what I bought
2021-10-13 changed board outline
2021-10-14 Schem Pictures
2021-10-14 through hole vias
2021-10-14 screenshots
2021-10-14 More screenshots
2021-10-14 Reset_Line
2021-10-14 Added reset button, fixed 7seg pin order
2021-10-14 Added Pullups to Daughterboard
2021-10-14 Updated Screenshots
2021-10-14 switched symbols
2021-10-14 Zipped Projs
2021-10-15 final Rev1 changes. increased heatsink area, flipped LEDs again, increased button mount hole size
2021-10-15 final final rev1 changes
2021-10-16 Some updates
2021-10-17 'switched uart'
2021-10-17 ''update"
2021-10-19 '3D LDO Model'
2021-10-20 Enhanced tracker code and added castling detection.
2021-10-20 added two more buttons
2021-10-20 edited main board headers for buttons, daughterboard power
2021-10-20 changed audio resistor value, same package
2021-10-20 changed 5V trace
2021-10-20 gerbers
2021-10-20 gerbers 2.0
2021-10-21 lab changes
2021-10-21 Updated LED, speaker, tracker code for pins on dev board
2021-10-21 ESD and Pullups
2021-10-21 Added Silkscreen info
2021-10-21 new main board gerbers
2021-10-22 minor tweaks
2021-11-11 Updated Button
2021-11-29 I really hope this doesn't break everything
2021-11-29 Removed extra pi file
2021-11-29 Added in improved tracker code with legal move detection and integration with LEDs. Added test for tracker with just one piece on the board.
2021-11-30 Added button EXTI callbacks and debouncing. Added more sophisticated test for legal piece detection.
2021-12-02 New stuff is in
2021-12-03 Increased quality of tracker initialization. Improved legal piece detection recovery.
2021-12-03 Evertyhing except castling and timer work
2021-12-03 Updated with most recent files
2021-12-03 Added support for switch interface. Implemented chess clock. Relocated AI invocation in tracker.c
2021-12-04 Castling works with AI. Timer gets updated with each AI move instead of each second for practice mode
2021-12-06 Fixed castling queen-side.
2021-12-06 Fixed playing piece from opposite team from switching the turn to them.
